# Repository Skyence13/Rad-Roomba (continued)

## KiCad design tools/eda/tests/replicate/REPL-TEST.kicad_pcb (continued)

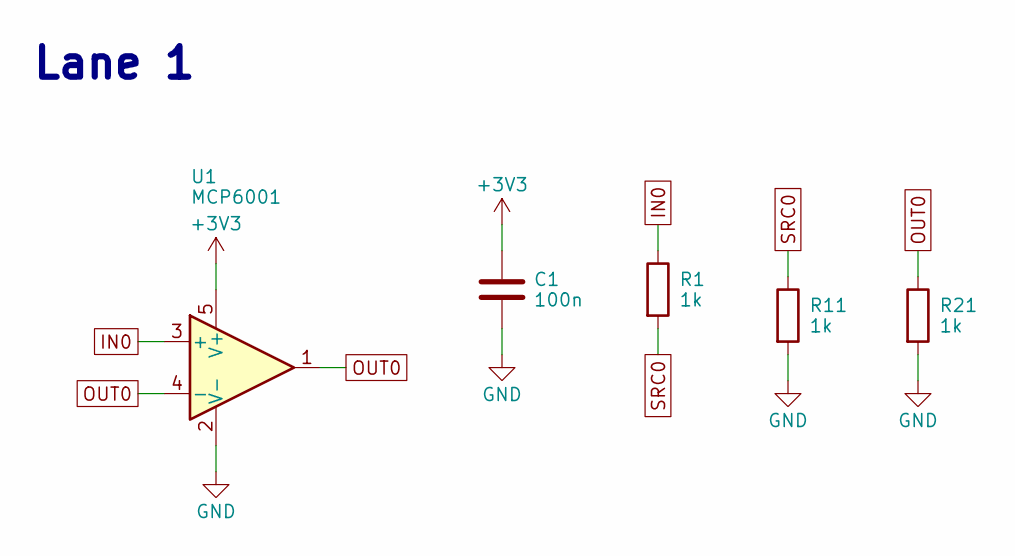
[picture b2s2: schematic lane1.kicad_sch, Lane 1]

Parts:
C1: 100n; C_0402_1005Metric; MPN GRM155R71C104KA88D
R1, R11, R21: 1k; R_0402_1005Metric; MPN RC0402FR-071KL
U1: MCP6001; SOT-23-5; MPN MCP6001T-I/OT

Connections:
+3V3: C1.1, U1.5 (V+); also elsewhere on the board
GND: C1.2, R11.2, R21.2, U1.2 (V-); also elsewhere on the board
IN0: R1.1, U1.3 (+)
OUT0: R21.1, U1.1, U1.4 (-)
SRC0: R1.2, R11.1

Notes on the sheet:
Lane 1

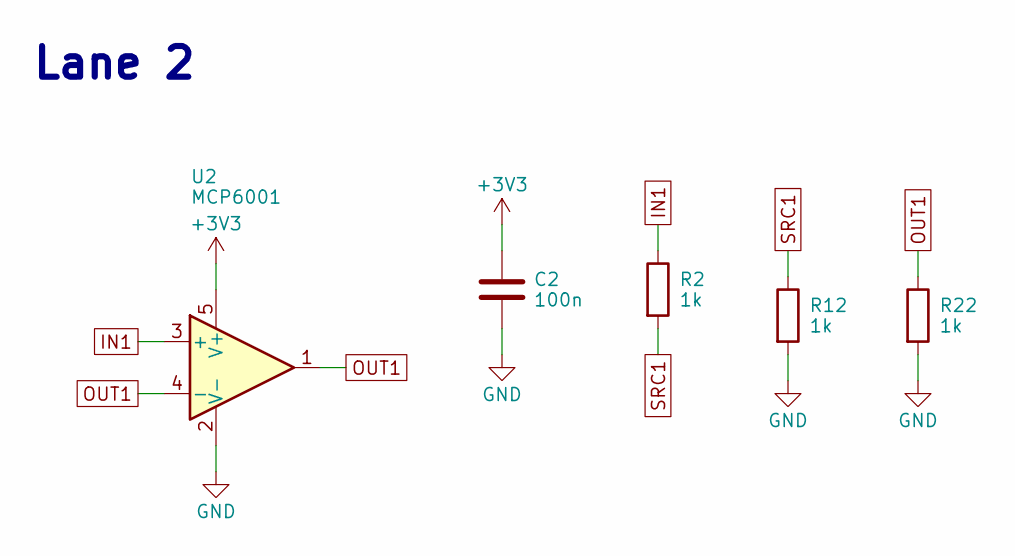
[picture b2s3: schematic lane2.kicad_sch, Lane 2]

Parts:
C2: 100n; C_0402_1005Metric; MPN GRM155R71C104KA88D
R2, R12, R22: 1k; R_0402_1005Metric; MPN RC0402FR-071KL
U2: MCP6001; SOT-23-5; MPN MCP6001T-I/OT

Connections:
+3V3: C2.1, U2.5 (V+); also elsewhere on the board
GND: C2.2, R12.2, R22.2, U2.2 (V-); also elsewhere on the board
IN1: R2.1, U2.3 (+)
OUT1: R22.1, U2.1, U2.4 (-)
SRC1: R2.2, R12.1

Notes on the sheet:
Lane 2

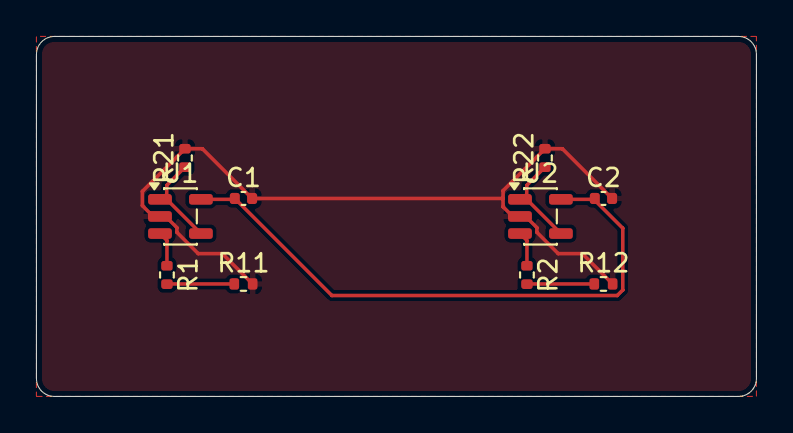
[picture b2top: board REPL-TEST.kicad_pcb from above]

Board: 2 copper layers, 40.0 x 20.0 mm, 10 parts (0 on the bottom side), 8 nets.

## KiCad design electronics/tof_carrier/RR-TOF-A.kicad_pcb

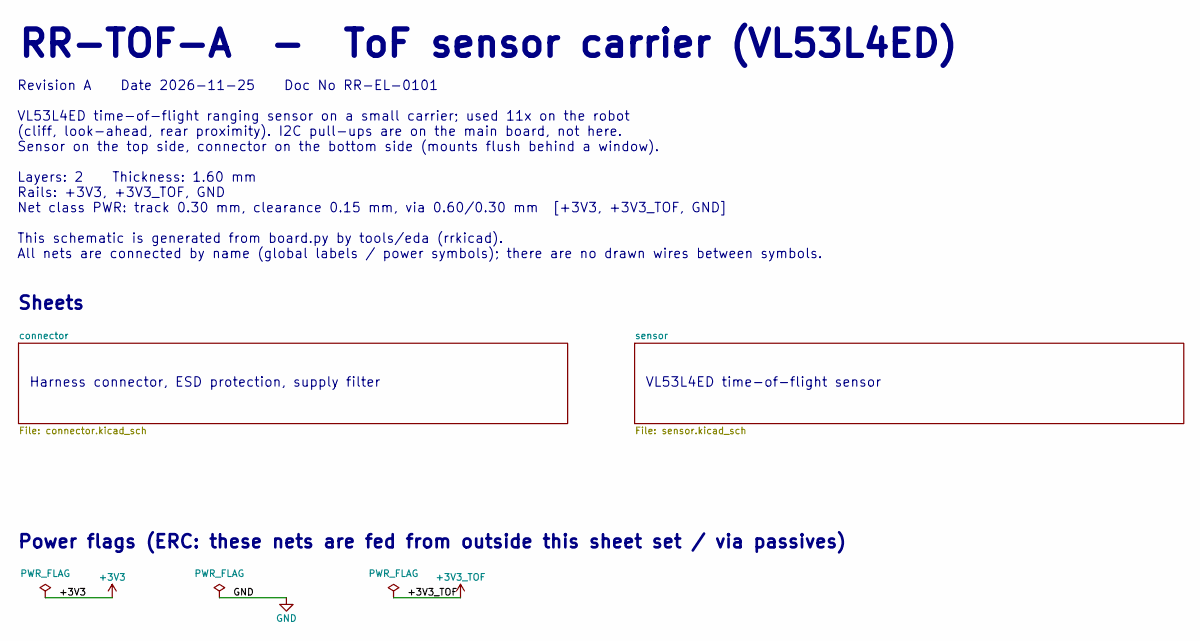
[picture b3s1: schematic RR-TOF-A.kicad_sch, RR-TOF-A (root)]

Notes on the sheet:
RR-TOF-A - ToF sensor carrier (VL53L4ED)
Revision A Date 2026-11-25 Doc No RR-EL-0101 VL53L4ED time-of-flight ranging sensor on a small carrier; used 11x on the robot (cliff, look-ahead, rear proximity). I2C pull-ups are on the main board, not here. Sensor on the top side, connector on the bottom side (mounts flush behind a window). Layer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
Sheets
Harness connector, ESD protection, supply filter
VL53L4ED time-of-flight sensor
Power flags (ERC: these nets are fed from outside this sheet set / via passives)

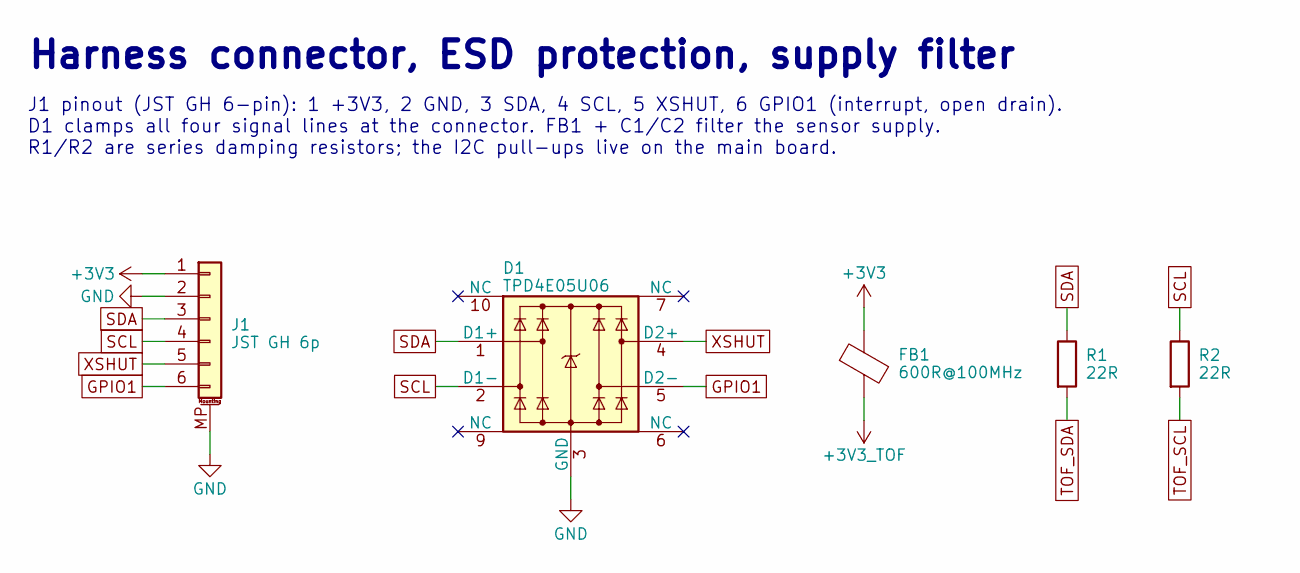
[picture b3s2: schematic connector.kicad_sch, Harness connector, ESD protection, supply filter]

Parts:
D1: TPD4E05U06; USON-10_2.5x1.0mm_P0.5mm; MPN TPD4E05U06DQAR
FB1: 600R@100MHz; L_0603_1608Metric; MPN BLM18AG601SN1D
J1: JST GH 6p; JST_GH_SM06B-GHS-TB_1x06-1MP_P1.25mm_Horizontal; MPN SM06B-GHS-TB(LF)(SN)
R1, R2: 22R; R_0402_1005Metric; MPN RC0402FR-0722RL

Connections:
+3V3: FB1.1, J1.1
+3V3_TOF: FB1.2; also elsewhere on the board
GND: D1.3 (GND), D1.8 (GND), J1.2, J1.MP (MountPin); also elsewhere on the board
GPIO1: D1.5 (D2-), J1.6; also elsewhere on the board
SCL: D1.2 (D1-), J1.4, R2.1
SDA: D1.1 (D1+), J1.3, R1.1
TOF_SCL: R2.2; also elsewhere on the board
TOF_SDA: R1.2; also elsewhere on the board
XSHUT: D1.4 (D2+), J1.5; also elsewhere on the board

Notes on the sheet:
Harness connector, ESD protection, supply filter
J1 pinout (JST GH 6-pin): 1 +3V3, 2 GND, 3 SDA, 4 SCL, 5 XSHUT, 6 GPIO1 (interrupt, open drain). D1 clamps all four signal lines at the connector. FB1 + C1/C2 filter the sensor supply. R1/R2 are series damping resistors; the I2C pull-ups live on the main board.

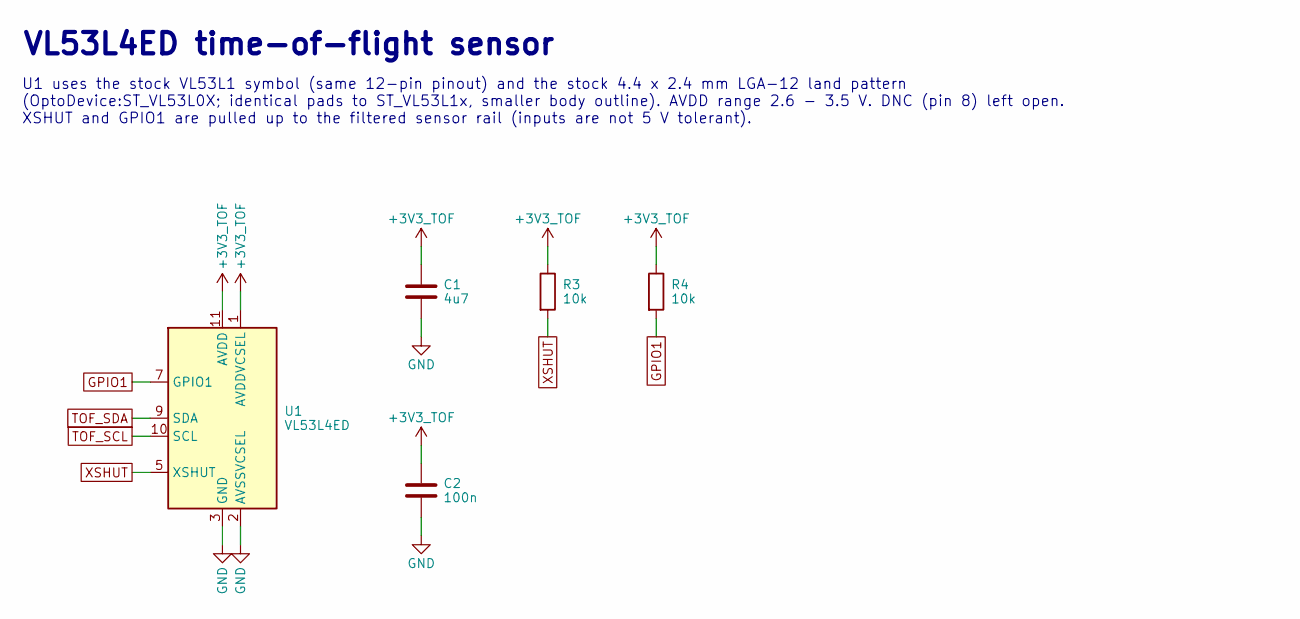
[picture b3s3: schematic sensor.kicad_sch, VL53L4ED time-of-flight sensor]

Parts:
C1: 4u7; C_0603_1608Metric; MPN GRM188R61A475KE15D
C2: 100n; C_0402_1005Metric; MPN GRM155R71C104KA88D
R3, R4: 10k; R_0402_1005Metric; MPN RC0402FR-0710KL
U1: VL53L4ED; ST_VL53L0X; MPN VL53L4EDV0DH/1

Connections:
+3V3_TOF: C1.1, C2.1, R3.1, R4.1, U1.1 (AVDDVCSEL), U1.11 (AVDD); also elsewhere on the board
GND: C1.2, C2.2, U1.2 (AVSSVCSEL), U1.3 (GND), U1.4 (GND), U1.6 (GND), U1.12 (GND); also elsewhere on the board
GPIO1: R4.2, U1.7 (GPIO1); also elsewhere on the board
TOF_SCL: U1.10 (SCL); also elsewhere on the board
TOF_SDA: U1.9 (SDA); also elsewhere on the board
XSHUT: R3.2, U1.5 (XSHUT); also elsewhere on the board

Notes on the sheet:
VL53L4ED time-of-flight sensor
U1 uses the stock VL53L1 symbol (same 12-pin pinout) and the stock 4.4 x 2.4 mm LGA-12 land pattern (OptoDevice:ST_VL53L0X; identical pads to ST_VL53L1x, smaller body outline). AVDD range 2.6 - 3.5 V. DNC (pin 8) left open. XSHUT and GPIO1 are pulled up to the filtered sensor rail (inputs are not 5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

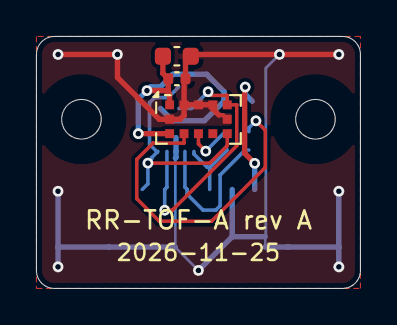
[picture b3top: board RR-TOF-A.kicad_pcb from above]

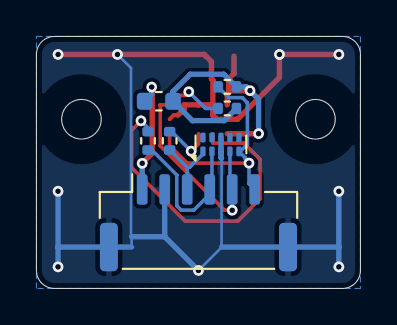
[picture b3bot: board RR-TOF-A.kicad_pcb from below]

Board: 2 copper layers, 18.0 x 14.0 mm, 12 parts (7 on the bottom side), 9 nets.

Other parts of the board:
H1, H2: M-hole 2.2mm; MountingHole_2.2mm_NPTH

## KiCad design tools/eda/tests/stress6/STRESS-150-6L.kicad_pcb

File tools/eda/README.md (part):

# rrkicad — scripted, headless KiCad 9 flow

One Python **board definition** (`electronics/<board>/board.py`) is the single source of
truth. From it the tool generates a native KiCad 9 project (schematic, PCB, project
file), autoroutes it, runs ERC/DRC and writes all fabrication / documentation outputs.
Nothing needs a GUI or network access; KiCad and Freerouting run in Docker.

```
python3 tools/eda/rrkicad.py build electronics/<board>/board.py   # everything
python3 tools/eda/rrkicad.py build .../board.py --no-route        # generate + check, no autorouter
python3 tools/eda/rrkicad.py build .../board.py --reroute         # ignore the cached route
python3 tools/eda/rrkicad.py sch   .../board.py                   # schematic + ERC + PDF only (fast)
python3 tools/eda/rrkicad.py check .../board.py                   # re-run ERC/DRC on the existing files
```
Options for `build`: `--passes N --threads N --timeout SEC` (override the definition's
autorouter settings), `--budget SEC` (wall-clock budget for all autorouter runs, see
"Long routing jobs"). Exit code 0 = pass, 1 = checks failed, 2 = definition error.

Requirements on the host: `python3`, `docker`, images `kicad/kicad:9.0` and
`ghcr.io/freerouting/freerouting:latest` (tested: KiCad 9.0.9, Freerouting 2.6.0).
Wrappers (use them for anything ad hoc, they handle mounts, uid and HOME):
`tools/docker/kicad.sh <cmd...>` and `tools/docker/freerouting.sh in.dsn out.ses [passes] [threads]`.
Both mount the repository at the same absolute path, run as the calling uid with
`--network none`, and work only on files inside the repository.

## What happens in a build

| step | where | what |
|---|---|---|
| 1 `_gen` | KiCad container | evaluate `board.py`; resolve symbols; write `.kicad_pro`, `sym-lib-table`, `fp-lib-table`, `rr_local.kicad_sym`, `rr_local.pretty/`, root + one `.kicad_sch` per group; export the KiCad netlist from the generated schematic and **cross-check it pin-by-pin against the definition**; build the unrouted `.kicad_pcb` with pcbnew (pad nets come from that netlist); auto-arrange unplaced parts; copy replicated blocks; plane fan-out vias; export `route/<name>.dsn` (with 25 um extra clearance and edge keep-outs for the autorouter) |
| 2 route | Freerouting container | `route/<name>.dsn` → `route/<name>.ses` (+ `freerouting.log`, `route_meta.json`). Skipped when the DSN hash is unchanged and a SES exists (so reruns are deterministic); `--reroute` forces it |
| 3 `_post` | KiCad container | import SES into the pristine generated board (separate process), verify pre-routes are untouched, replay `route/finish.json`, widen tracks the router necked below the fab minimum, remove dangling stubs (and unused escape vias on a fully connected board), fill zones, add fab notes/dimensions, save; ERC; DRC with schematic parity; outputs; `reports/summary.json`, `reports/open_connections.txt` |
| 4 continue / restart | both | only while connections are open: continue runs from the routed board, fresh restarts with other seeds, optionally within `--budget` (quick imports in between, best SES kept; see "Completion strategy" and "Long routing jobs") |
| 5 finisher | KiCad container | only while connections are still open: maze router with rip-up, then step 3 again |

Files per board directory:
```
board.py                       the definition (edit this, nothing else)
<name>.kicad_pro/.kicad_sch/.kicad_pcb, <group>.kicad_sch, rr_local.*, *-lib-table, 3d/   generated KiCad project
route/      <name>.dsn, <name>.ses (routing result = cache key + source of the tracks), freerouting.log,
            route_meta.json, progress.log (one JSON line per autorouter run), finish.json (finisher
            result), blocks.json (replicate), escape_vias.json (intermediate)
reports/    erc.json/.rpt, drc.json/.rpt, summary.json, placement.txt, build_state.json
out/        <name>-schematic.pdf, gerber/ (Gerbers, Excellon PTH/NPTH, drill maps, .gbrjob),
            <name>-pos.csv, <name>-bom.csv, <name>-fab.pdf, <name>-assembly-top/bottom.pdf,
            <name>-copper.pdf, <name>.step, <name>-render-top/bottom.png, pinmap.json, <name>.net
```
`reports/summary.json`: `status` (`pass`/`fail`), `fail_reasons`, ERC/DRC error/warning
counts by type, `unconnected`, `parity`, `unrouted_nets`, every waiver with its
justification and match count, auto-added `pwr_flags`, `single_pin_nets`, BOM lines
missing an MPN or flagged `verify`, routing statistics, and the output list.
**Fail** = any ERC error, DRC error, unconnected item or schematic-parity item that is
not waived. Warnings never fail the build but are counted.

`out/pinmap.json`: for every part pin: `pin`, `name`, `net` (null = no-connect), `type`,
`pad_xy_mm` (board frame) and `side`; plus a `nets` → `["REF.pin"]` index.

## Conventions

* Units: mm. **Board frame: X right, Y up**, origin = the point you define the outline
  against; it becomes the KiCad drill/place (aux) origin and grid origin, so
  `board.py`, the pick-and-place file, the STEP model and `pinmap.json` share coordinates.
* `at=(x, y, rot, side)`: `rot` is the KiCad footprint orientation in degrees (CCW
  positive), `side` `"F"` or `"B"`. For bottom parts it is the value KiCad shows for the
  flipped footprint — check the result in `pinmap.json` (`pad_xy_mm`) rather than guessing
  (e.g. the JST GH on RR-TOF-A needed `rot=180` on the bottom to face the edge).
* Net names are global: the same string anywhere is the same net. PCB net names equal
  the names in `board.py`.
* Schematic style: one A3 sheet per group (extra sheets are added automatically when a
  group overflows). Every used pin has a short stub ending in a global label, or a power
  symbol for nets declared with `board.rail()`. Unused pins get no-connect flags. Nets
  that have power-input pins but no power-output pin get a `PWR_FLAG` on the root sheet
  (listed in the summary as `pwr_flags`).
* Reference designators are yours to assign; they must be unique.
* Every symbol pin must be either in `pins`, in `nc`, of type no_connect, or the part
  must say `unused="nc"`; otherwise the build stops and lists the pins.

## Board definition by example

```python
from rrkicad import Board, Pad, SymPin, Rules

board = Board("RR-XYZ-A", title="Example board", rev="A", date="2026-11-25", docnum="RR-EL-0123",
              company="Rad Roomba", layers=4,          # 2, 4 or 6:
                                                        #   4 = F.Cu sig / In1 plane / In2 plane / B.Cu sig
                                                        #   6 = F.Cu sig / In1 GND / In2 sig / In3 sig / In4 PWR / B.Cu sig
              thickness=1.6, silk_refs=True,            # False hides all reference designators on silk
              rules=Rules(),                            # fab rules, see "Rules" below
              paper="A3", description="free text shown on the root sheet")

# --- nets ----------------------------------------------------------------------
board.rail("+5V", "+3V3", "GND")                      # drawn with power symbols (stock power:<name> or generated)
board.netclass("PWR", ["+5V", "+3V3", "GND", "VBAT*"],  # exact names or KiCad wildcards
               track=0.4, clearance=0.2, via_dia=0.8, via_drill=0.4)

# --- parts: one group = one schematic sheet --------------------------------------
g = board.group("mcu", "Microcontroller", notes="Text block printed at the top of the sheet.")
g.part("U1", "MCU_ST_STM32G4:STM32G474RETx", "STM32G474RET6",        # ref, symbol, value
       footprint=None,                      # default: the symbol's Footprint property
       mfr="STMicroelectronics", mpn="STM32G474RET6",
       pins={"VDD": "+3V3", "VSS": "GND",   # key = pin NAME (all pins with that name) ...
             "7": "NRST", "PA0": "ADC0"},   # ... or pin NUMBER (numbers win)
       nc=["PC13"], unused="nc",            # explicit NC pins; unused="nc" marks all remaining pins NC
       at=(50, 40, 0, "F"),                 # omit -> auto-arranged
       notes="BOM note", verify=True,       # verify=True -> "verify: true" in the BOM notes
       dnp=False, bom=True, datasheet="https://...", description="...",
       fields={"Tolerance": "1%"},          # extra symbol/footprint fields
       sch_rot=0,                           # symbol rotation on the sheet (0/90/180/270)
       silk_ref=False,                      # per part: False | True | (x, y[, rot[, size]])
       zone_connect="solid",                # pads of this part: "solid" | "thermal" | "none"
       height=1.6,                          # body height (mm) for the generated 3D envelope, see "3D"
       model=None)                          # or a real model: "${KIPRJMOD}/3d/part.step"
g.C("C1", "100n", "+3V3", "GND", pkg="0402", mfr="Murata", mpn="GRM155R71C104KA88D", near="U1.16")
g.R("R1", "10k", "+3V3", "NRST", mfr="Yageo", mpn="RC0402FR-0710KL")           # pkg default 0402
g.FB("FB1", "600R@100MHz", "+3V3", "VDDA", pkg="0603", mfr="Murata", mpn="BLM18AG601SN1D")
g.L("L1", "10u", "SW", "VOUT", pkg="0805", mfr="...", mpn="...")
g.LED("D1", "green", "LED_A", "GND", pkg="0603", mfr="...", mpn="...")       # anode, cathode
# R/C/L/FB/LED accept every part() keyword (at=, near=, dnp=, ...).  pkg: 0201 0402 0603 0805 1206 1210 2010 2512

# identical blocks: place (or auto-arrange) one block, copy its placement AND routing at an offset
# (see "Replicating blocks" below)
# board.replicate((lane1_group, lane2_group), dx=80.0, dy=0.0)     # groups with the same parts in the same order
# board.replicate({"U1": "U101", "C1": "C101"}, dx=80.0)          # or an explicit {source_ref: destination_ref} map

# auto-arrange hints for parts without at=:
#   near="U1" | near="U1.16" (pad 16 of U1)   edge="left|right|top|bottom"   side="B"   rot=90 (fixed rotation)
# rail-to-rail capacitors without near= are spread over the supply pins of the ICs in their group.

# --- outline, holes, copper ------------------------------------------------------
board.outline_rect(100, 80, radius=2.0, origin="corner")   # origin "corner" (lower-left) or "center"
# board.outline_poly([(x, y), ...], radius=1.0)            # any closed polygon, every corner rounded
board.cutout_rect(50, 76, 12, 3, radius=1.0)               # centre x, y, w, h   (also cutout_circle, cutout_poly)
board.hole("H1", 4, 4, drill=3.2, keepout=7.0)             # NPTH + circular keep-out (tracks/vias/pour/parts)
board.hole("H2", 96, 4, drill=3.2, plated=True, pad=6.0, net="GND")
board.zone("GND", ["In1.Cu"], connect="solid")             # polygon=None -> whole board
board.zone("+3V3", ["In2.Cu"], connect="solid")
board.zone("+5V", ["In2.Cu"], polygon=[(0, 0), (30, 0), (30, 30), (0, 30)], priority=1)  # plane split
board.zone("GND", ["F.Cu", "B.Cu"])                        # pours; options: clearance, min_width,
                                                           # connect thermal|solid|none, thermal_gap/width, islands
board.keepout("KO_ANT", polygon=[(80, 60), (92, 60), (92, 72), (80, 72)],   # or circle=(x, y, dia)
              layers=("*.Cu",), tracks=True, vias=True, copper=True, pads=False, footprints=True)
board.track("XTAL_IN", [(10, 10), (12, 10), (13, 11)], layer="F.Cu", width=0.2)  # pre-route: locked, kept by the router
board.via("GND", 20, 20)                                   # pre-route via (net-class size unless dia=/drill=)
board.text("{name} rev {rev} {date}", 50, 2, layer="F.SilkS", size=1.0)   # also {title} {docnum}; B.* is mirrored
board.fab_note("Controlled impedance not required.")       # extra line on the fabrication drawing

# --- project-local library (parts missing from the stock libraries) -----------------
sym = board.symbol("MYSENSOR", [SymPin(1, "VDD", "power_in", "T"), SymPin(2, "OUT", "output", "R"),
                                SymPin(3, "GND", "power_in", "B"), SymPin(4, "EN", "input", "L")],
                   ref_prefix="U", datasheet="https://...")                  # -> "rr_local:MYSENSOR"
fp = board.footprint("MYSENSOR_LGA4", [Pad(1, -1.0, -0.8, 0.6, 0.9), Pad(2, 1.0, -0.8, 0.6, 0.9),
                                       Pad(3, 1.0, 0.8, 0.6, 0.9), Pad(4, -1.0, 0.8, 0.6, 0.9)],
                     body=(2.0, 1.2))                                        # -> "rr_local:MYSENSOR_LGA4"
g.part("U9", sym, "MYSENSOR", fp, mfr="...", mpn="...", pins={"VDD": "+3V3", "OUT": "S1", "GND": "GND", "EN": "+3V3"})

# --- autorouter / auto-arrange / waivers ---------------------------------------------
board.route(passes=100, threads=None, timeout=None, optimizer=True, enabled=True, extra_args=[],
            plane_fanout=True,     # rrkicad's own track+via beside every SMD pad of plane nets (see Routing notes)
            retries=2,             # extra "continue" autorouter runs while connections are open
            restarts=1,            # then fresh autorouter runs with another item-order seed (best result kept)
            fanout=False,          # Freerouting's own fan-out stage (escape via on every SMD pin; rarely useful)
            escape="auto",         # fine-pitch escape (see Routing notes): "auto" = on for 4/6 layers, True, False
            escape_pitch=0.65,     #   ICs whose pad pitch is below this get escaped ...
            escape_min_pads=16,    #   ... and that have at least this many perimeter pads
            escape_via=None,       #   (dia, drill) of escape vias; default = the fab minimum via of Rules
            escape_track=None,     #   stub width; default Rules.min_track
            escape_layers=None,    #   informational: target layer recorded per via (through vias reach all layers)
            escape_direct=True,    #   short direct pre-route to a nearby two-pad passive instead of a via
            finisher=True,         # built-in maze router for the last open connections (see Routing notes)
            finisher_ripup=True,   #   ... allowed to rip up and reroute autorouter copper of other signal nets
            finisher_seconds=900,  #   ... time budget
            budget=None,           # wall-clock budget (s) for all autorouter runs (also: build --budget SEC)
            chunk=900,             #   with a budget: cap per Freerouting run (each run leaves an SES on disk)
            stall=2,               #   with a budget: stop after this many continue runs without improvement
            zone_nets="auto",      # "auto" = "exclude" on 4/6 layers: nets with a copper zone are never autorouted
            fr_fallback="none")    # Freerouting's own fallback strategies after stagnation (see Routing notes)
# per part: g.part(..., escape=None | True | False)   None = decided by pad pitch, True = force, False = never
board.autoplace_options(clearance=0.3, ic_halo=2.0, edge_margin=0.5, grid=0.25, spread=0.35, rotations=(0, 90, 180, 270),
                        escape_keepaway=2.0)   # free band (mm) around the courtyard of escaped ICs (auto-arranged neighbours)
board.waive("drc", "silk_overlap", "Reference text overlaps on the dense RF corner; assembly uses the Fab layer.",
            match=r"R1[0-9]")                             # regex on the violation text; None = all of that type
board.severity("drc", "silk_over_copper", "ignore", "Silk is clipped by the fab's solder-mask subtraction.")
```
The file must leave the `Board` in a module-level variable named `board`. It is plain
Python evaluated **inside the KiCad container** (Python 3.11): loops, helper functions
and `from rrkicad.symlib import SymbolLibs` (to look at stock symbol pins) are fine.

### Stock libraries
Symbols `Library:Name` and footprints `Library:Name` refer to the KiCad 9 stock
libraries in the container (`/usr/share/kicad/symbols`, `/usr/share/kicad/footprints`).
Unknown names stop the build with close-match suggestions. To browse:
`tools/docker/kicad.sh bash -c 'ls /usr/share/kicad/footprints/Package_SO.pretty | head'`,
or print a symbol's pins:
```
tools/docker/kicad.sh python3 -c "from rrkicad.symlib import SymbolLibs
for p in SymbolLibs().get('Device:R').pins: print(p.number, p.name, p.etype, p.unit)"
```
Multi-unit symbols are placed unit by unit automatically (map their pins by number).
Derived symbols (`extends`) are flattened like KiCad does.

### Local symbols / footprints
* `SymPin(number, name, etype="passive", side="L", unit=1)` — `etype` is a KiCad pin
  type (`input output bidirectional tri_state passive power_in power_out open_collector
  open_emitter no_connect unspecified free`); `side` L/R/T/B, pins are stacked in list
  order at 2.54 mm pitch; several `unit` values make a multi-unit symbol.
* `Pad(number, x, y, w, h=None, shape="roundrect", kind="smd", drill=None, rot=0, rratio=0.25, paste=True)`
  — coordinates in the **footprint editor frame (x right, y DOWN, top view)**; `shape`
  rect/roundrect/circle/oval; `kind` smd/thru/npth. `board.footprint(..., body=(w, h),
  courtyard=(w, h), pin1=True, model="${KIPRJMOD}/3d/x.step")`. Fab outline, courtyard,
  silk lines clear of pads and a pin-1 dot are generated. A footprint without pads (e.g. a
  shield-can outline) is allowed when it has `body=` or `courtyard=`.
* Mounting holes from `board.hole()` are generated footprints in `rr_local.pretty`
  (board-only, no courtyard; the keep-out rule area protects them).
* Generated rail symbols (rails with no stock `power:` symbol) also live in `rr_local.kicad_sym`.

### Rules
`Rules(min_track=0.15, min_clearance=0.15, min_via_dia=0.6, min_via_drill=0.3, min_annular=0.13,
edge_clearance=0.3, min_hole=0.3, min_hole_clearance=0.25, min_hole_to_hole=0.25, track=0.2,
clearance=0.15, via_dia=0.6, via_drill=0.3, min_silk_text=0.8, min_silk_thickness=0.1)` —
written to the project's board setup and the `Default` net class; `netclass()` adds
classes on top (first matching pattern wins).

## Routing notes
* **Plane fan-out (4/6 layers).** For every net that has a zone on a plane layer
  (`In1/In2` on 4 layers, `In1/In4` on 6) the PCB step itself adds a short locked track
  and a via beside each SMD pad of that net (through-hole pads connect to the plane
  directly). The via respects copper clearance, hole-to-hole, edge clearance, cut-outs,
  via keep-outs and other parts' courtyards where possible, and must land inside its
  own net's plane polygon (split planes). Clearances are pairwise (the larger of both net
  classes, like KiCad's DRC); footprint-internal rule areas and copper drawn inside
  footprints (net ties) are obstacles. Exposed/thermal pads get their via in the pad centre.
  **Long fan-out:** a pad with no legal via position beside it is connected by the maze
  router (see Finisher) to the nearest legal via position inside its own plane polygon
  (windows 5 / 12 / 30 mm), as locked pre-route; `summary.json` → `routing.plane_fanout`
  lists them (`long_fanout`) and the pads still without a connection (`failed`, with the
  reason). After zone fill, KiCad's DRC connectivity check is what confirms every plane
  connection (`unconnected` must be 0).
* **Zone nets are not autorouted (4/6 layers, `zone_nets="auto"`).** Every net that has a
  copper zone is moved into a DSN net class `RR_ZONE_<class>` that Freerouting is told to
  ignore (`--router.autorouter.ignore_net_classes`); its pads connect through the plane
  fan-out / long fan-out and the zone fill only. Whatever stays open is left to the finisher
  and reported. On 2-layer boards (`"auto"` = `"route"`) zone nets are routed as tracks and
  the pour is added afterwards (RR-TOF-A, RR-PANEL).
  Split planes must be **non-overlapping polygons** (Freerouting rejects overlapping
  plane areas; do not rely on zone priority for splits).
  If you also pour a plane net on the outer layers, use `connect="solid"` for that pour
  (or leave the outer layers unpoured): thermal spokes next to fan-out tracks get starved.
* **Fine-pitch escape (4/6 layers by default).** Before routing, every IC whose pad pitch is
  below `escape_pitch` (0.65 mm; QFP, QFN, TSSOP-0.5, ...) and has at least
  `escape_min_pads` (16) perimeter pads, or that has `escape=True`, gets
  its pin escapes as locked pre-routes (`rrkicad/escape.py`):
  - signal pads: a short stub (`escape_track`, default `min_track`) out of the pad tip and a
    via on a ring outside the package, alternating between two staggered radii. The ring is
    *fanned*: neighbouring vias are spaced by via radius + half stub + clearance of the two
    nets, so the stub of an outer-row via passes between two inner-row vias with full
    clearance even with 0.6 mm vias at 0.5 mm pitch (the inner radius grows until every
    outer stub clears its neighbours' vias). Pads whose planned spot is blocked get a local
    search over further radii / lateral offsets, then (packages without exposed pad) a
    position under the package;
  - plane-net pads: via *under* the package for QFP-like parts (keeps the ring free),
    otherwise a ring position whose via lies inside the net's own plane polygon;
  - pads whose net reaches a two-pad passive (pull-up, series R placed `near=` the pin)
    within 4 mm: a direct pre-route to that pad instead of a via, when one or two straight
    segments do it with clearance (`escape_direct`);
  - skipped (listed with the reason in `summary.json` → `routing.escape.skipped`):
    no-connect pins, pins tied only to an adjacent pin, square/round pads (BGA), and pads
    with no legal position (left to the autorouter, also listed as a build note; for zone nets on
    4/6 layers: left to the finisher).
  All checks are exact geometry (`rrkicad/geom.py`): copper clearance of both net classes
  + the 25 um DSN margin, hole-to-hole, hole clearance, board edge, cut-outs, via
  keep-outs, other parts' courtyards (vias stay outside them), existing fan-out vias. The
  items are exported to the DSN as fixed wiring *of their net*, so Freerouting starts from
  the escape vias. `summary.json` → `routing.escape`: per part pitch / ring / inward / direct
  / skipped counts, totals, via and stub size. Escape vias the router did not use (it
  connected at the pad instead) are removed with their stub after the SES import (only
  escape vias, only if connectivity does not get worse). The escape runs before the plane
  fan-out; the plane fan-out puts a via in the centre of exposed/thermal pads.
  Small fine-pitch parts (< 16 pads: USON-10 ESD arrays, SOT-563, ...) are left to the
  autorouter by default: it escapes them reliably, and a via ring around a flow-through
  ESD array works against its layout; force one with `escape=True`.
  The auto-arranger keeps `escape_keepaway` (2 mm) free around
  escaped ICs; explicitly placed neighbours are the author's responsibility (a pad whose
  via would land in a neighbour's courtyard is skipped and reported).
* **Finisher.** If connections are still open after the autorouter (and its continue runs),
  `finisher=True` runs a plain grid maze router (A*, 0.05 mm grid, 8 directions, through
  vias between signal layers, never on plane layers) for each open connection KiCad's DRC
  reports, on a clearance-inflated occupancy grid (both net classes' clearance + half the
  track width; vias against copper on every layer, drills, same-net SMD pads; edge,
  cut-outs, keep-outs), in a window that grows 6 mm -> 15 mm -> whole board. Every path is
  re-checked with exact geometry before it is added. If there is no free path and
  `finisher_ripup=True` (default), it searches again allowing to cross *unlocked autorouter
  copper of other signal nets* at a cost, rips up what the new path violates, and
  reconnects every ripped net (which may in turn rip up further autorouter copper, never
  pre-routes, escape/fan-out copper, nets with zones or the finisher's own new copper);
  at most 40 steps per open connection (`finisher_seconds` caps the whole finisher), and the whole transaction is undone if any ripped
  net cannot be reconnected. Results go to `route/finish.json`
  (added items and ripped-up items, keyed to the SES hash, re-applied on cached builds; keep
  it under version control with the SES); `summary.json` → `routing.finisher` lists what it routed and what not and why.
  DRC checks the result like everything else; nothing is ever marked connected by the
  finisher itself. Slow in Python on large windows (minutes per hopeless connection).
* Freerouting reports "N pin-to-pin clearance violations" in `route/freerouting.log` for
  QFN exposed pads vs. their perimeter pads: that is the footprint's own pad spacing under
  the 25 um DSN margin, fixed items it cannot change; KiCad DRC is the reference.
* Freerouting's fallback strategies after stagnation (default chain ending in
  `continue-auto-neck`; even `continue` re-routes from the initial board) can eat the whole
  timeout: rrkicad passes `--router.autorouter.fallback_strategies=none` unless
  `route(fr_fallback=...)` or `extra_args` say otherwise - its own continue runs and restarts
  do that job and keep the best result.
* The autorouter gets keep-out bands along the outline and around cut-outs so routed
  copper keeps the board-edge clearance, and via keep-outs (plus track keep-outs on their
  layer, minus the tie's pads) over copper drawn inside footprints (net ties) - Freerouting
  does not see that copper. Rule areas that ban neither tracks nor vias (e.g. a "no
  footprints" area) are not exported to the router (KiCad would export them as full
  routing keep-outs).
* Pre-routes (`board.track`, `board.via`) and the plane fan-out are locked, exported as
  fixed, and verified after the SES import; the build fails if the router changed them.
* **Completion strategy.** If connections are still open after the first run, the build
  automatically lets Freerouting *continue from the routed result* (new DSN from the
  routed board; fresh rip-up budget concentrated on the failed nets), up to
  `retries` times, keeping a run only if it reduces the open count. Each continue run uses
  a different Freerouting item-order seed (`--router.autorouter.item_order_seed`); a run
  that does not improve is discarded and the next seed is tried. If connections are still
  open after that, Freerouting starts once more from scratch with another item-order seed
  (`restarts`, default 1; a fresh run is deterministic for a given DSN and seed, so repeating
  it unchanged is pointless) followed by its own continue runs; the result with fewer open
  connections is kept. Then the finisher (below) takes what is left. Freerouting itself
  also switches strategy when it stagnates (visible in `route/freerouting.log`).
  What is still open afterwards is reported, never hidden: `summary.json` →
  `drc.unrouted` lists every open connection with net, both end items and their board
  coordinates (also printed as `OPEN ...` lines), `routing.autorouter.attempts` lists
  the runs. A board with open connections is always FAIL.
* Giving Freerouting a `timeout` is safe: it is passed as Freerouting's own job timeout
  (verified: it stops and still writes the result); a hard kill follows 3 min later.
* The routing result lives in `route/<name>.ses` (+ `route_meta.json` with the DSN
  hash). Keep both under version control: with an unchanged definition the build
  re-uses them and reproduces the same PCB. `route/<name>.unrouted.kicad_pcb` is an
  intermediate file and need not be kept.

## Long routing jobs (large boards)
`python3 tools/eda/rrkicad.py build board.py --budget 2400` (or `route(budget=2400)`):
* every Freerouting run is capped at `chunk` seconds (default 900) and writes a scratch SES;
  it is imported with a quick import (connectivity count only, no ERC/DRC/outputs) and
  replaces `route/<name>.ses` only if it leaves fewer connections open. So
  `route/<name>.ses` always holds the best state so far - an interrupted job loses at most
  the run in progress; a later plain `build` re-uses it (DSN unchanged);
* after the first run, continue runs resume from the best routed board (new DSN exported
  from it), each with another item-order seed, until the budget is used up (less than
  3 min left) or `stall` runs in a row did not improve; then `restarts` fresh runs if time
  is left; then the finisher (its own `finisher_seconds`); then one full check;
* `route/progress.log`: one JSON line per run (kind, seed, seconds, open count, kept, best,
  elapsed) - `tail -f` it to watch an unattended job;
* the count used everywhere is KiCad's connectivity count after zone fill (`summary.json` →
  `drc.unconnected`; `drc.unconnected_listed` is how many KiCad's DRC report lists, it stops
  at 499).

### Recommended recipe for the final runs on the large boards
1. Placement first: every plane pad needs a via spot within ~4 mm (check `summary.json` →
   `routing.plane_fanout.failed` after `build --no-route`; aim for 0), 2+ mm free around
   fine-pitch ICs if escape is used, no DRC errors before routing.
2. Hand pre-routes (`board.track` / `board.via`) for power trunks, HV, analogue, safety chain.
3. Route lane 0 / the source block, then freeze it with `replicate()` (second build).
4. Unless step 1 reached 0, keep zone nets routable: `route(zone_nets="route")`.
   Escape: `escape="auto"` helps where the fine-pitch ICs have room (stress boards);
   if `routing.escape.skipped` lists many "no legal escape position", use `escape=False`.
5. One long run per DSN: `route(timeout=7200, passes=500, retries=2, restarts=0,
   optimizer=False)` and `build board.py` (no `--budget`): one uninterrupted Freerouting job,
   then continue runs from its result. Use `--budget SEC` (chunks of `chunk` s) only when
   the job must survive interruptions - the best SES is then on disk after every chunk.
6. Watch `route/progress.log`; results: `reports/summary.json` (`drc.unconnected`, `drc.errors`,
   `drc.by_type`), `reports/open_connections.txt` (KiCad's list, max 499), `route/<name>.ses`.
   A later `build` with an unchanged DSN re-uses the SES (and `route/finish.json`) without
   routing; `build --reroute` starts again.
7. Finish the remaining tens of connections in KiCad.

## Replicating blocks (identical lanes/channels)
`board.replicate(pairs, dx, dy, routes=True)` — `pairs` is `{source_ref: destination_ref}`
or a `(source_group, destination_group)` tuple (same parts in the same order).
* Placement: every destination part takes its source's position + (dx, dy), same rotation
  and side. The source block may be placed explicitly or auto-arranged; destinations
  are excluded from auto-arrange. Call it once per copy (lane 0 → 1, 0 → 2, 0 → 3).
* Routing (`routes=True`, default): after each routed build the tracks/vias of the
  **block-internal nets** (nets whose pins all belong to the source parts; rails and
  inter-block nets are excluded) are stored in `route/blocks.json`. The *next* build adds
  them as fixed pre-routes for the source block and, shifted and renamed, for each copy.
  So: build once (autorouter routes everything), build again (blocks frozen and
  identical; the autorouter only has plane leftovers and inter-block nets). If the
  source placement changes, the stored routes are ignored with a note and refreshed by
  the next build. Keep `route/blocks.json` under version control.
* Plane fan-out / escape are generated per pad for the copies as usual and are *not* stored in
  `blocks.json` (only router copper and the definition's own pre-routes are); a stored item
  identical to copper already on the board (e.g. a pre-route the definition draws for every
  lane itself) is not replayed again. (Before 2026-11-27 both happened and gave co-located
  vias; such an old `blocks.json` heals on the next routed build.) Overlaps of a copy with
  foreign parts, tracks or keep-outs show up in DRC, they are not checked at copy time.
* Auto-arrange: when a source part is auto-arranged, the spots of all its copies must be
  free as well and are reserved, so no other part lands where a copy will go.
Tested on `tools/eda/tests/replicate/` (2 lanes, 2 layers) and on a copy of RR-HEAD-ACQ
(`tools/eda/tests/head_escape/`, 4 lanes).

## Importing a stage-1 circuit definition
`rrkicad.importer.from_circuit(board, "design/circuit.py", ...)` converts a tool-neutral
`PARTS` list (dicts with `ref, value, mpn, manufacturer, description, package,
symbol_hint, footprint_hint, pins={pin_number: (pin_name, net) | None}, block, dnp,
notes`, optional `verify`, `height_mm`) into groups (one per `block`) and parts:
```python
from rrkicad import Board
from rrkicad.importer import from_circuit
board = Board("RR-CHS-MAIN", title="...", layers=6, ...)
report = from_circuit(board, os.path.join(os.path.dirname(__file__), "design/circuit.py"),
                      footprints={"U10": "Package_DFN_QFN:...", "MICROFIT-2x2-RA": "Connector_Molex:..."},  # by ref or package
                      symbols={"U42": "rr_local:MYSYM"},        # override the symbol of single parts
                      place={"J_PWR": (8, 50, 90, "F")},        # at= by ref (everything else is auto-arranged)
                      titles={"mcu": "Microcontroller"},        # sheet titles by block
                      allow_missing=False)                      # True: skip parts that have no footprint yet
board.rail("GND", "+3V3", ...); board.netclass(...); board.outline_rect(...); ...
```
Symbol per part: `symbols[ref]`, else `symbol_hint` if that stock symbol exists, has all
pin numbers used and no conflicting stacked pins (a hint `rr_local:NAME` is accepted when
`board.symbol("NAME", ...)` was defined before the import and has all pin numbers), else a
generated local box symbol (all
pins `passive`, named from the MPN). Pins with `None` become no-connects. `report` lists
`hint_rejected` (with the reason), `local_symbols`, `missing_footprints`. Parts can be
tuned afterwards: `board.part("U1").at = ...` is not supported - pass `place=`; other
attributes (`near`, `side`, `edge`, `zone_connect`, `silk_ref`) may be set on
`board.part(ref)` before the build. Reference designators are taken as they are
(`J_PWR`, `R_SH1` work).

Measured (schematic + ERC only, `python3 tools/eda/rrkicad.py sch tools/eda/tests/import_<x>/board.py`):

| circuit.py | parts imported | stock / generated symbols | hints rejected | no footprint | sheets | ERC | time |
|---|---|---|---|---|---|---|---|
| chassis_main (768) | 753 | 710 parts / 18 symbols | 46 | 15 | 18 | 0 errors, 112 warnings | 14 s |
| panel (24) | 24 | 24 / 0 | 0 | 0 | 6 | 0 errors, 0 warnings | 3 s |
| head_acq (1085) | 1081 | 971 parts / 20 symbols | 114 | 4 | 22 | 0 errors, 57 warnings | 17 s |

`reports/import_report.json` in each test directory lists every rejected hint with the
reason (mostly symbol names that do not exist in the stock library, with the closest
matches) and every part without a footprint - that list is the stage-2 to-do list.
Generated symbols have all-passive pins, so ERC cannot check pin directions on them.
No PCB was built from these imports (no placement, rails or outline decisions yet).

## Reproducibility
UUIDs are derived from hashes (schematic) or a seeded generator (PCB), ordering is
stable, report dates are stripped, Gerber/drill/STEP creation dates are set to the board
date. Re-running an unchanged definition reproduces identical KiCad project files.
Not byte-stable: PDFs and PNGs (embedded timestamps) and a *new* Freerouting run (its
optimiser is multi-threaded) — which is why the SES is cached.

## Known limitations
* No drawn wires in the schematic: connectivity is by label/power symbol only (readable,
  but not a hand-drawn schematic). No buses, no hierarchical pins, no symbol mirroring.
* Net labels are always global; there is no per-sheet local net scope.
* 2, 4 or 6 copper layers; through vias only; no differential-pair or length tuning
  (net-class diff-pair fields are written but the autorouter ignores them).
* Fine-pitch escape handles perimeter packages (QFP/QFN/SO/TSSOP); BGA (round pads) is
  skipped. Escape vias are through vias (no blind/buried/micro vias).
* Auto-arrange is a greedy helper (top/bottom side per part, courtyard rectangles). It
  avoids overlaps and keep-outs but knows nothing about signal integrity; place
  connectors, sensitive analogue parts and anything mechanical explicitly.
* `waive()` is tool-level: the item is listed as waived in `summary.json` but the KiCad
  GUI will still show it. `severity()` changes the project rule severity and is visible
  in the GUI too. Both require a written reason.
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
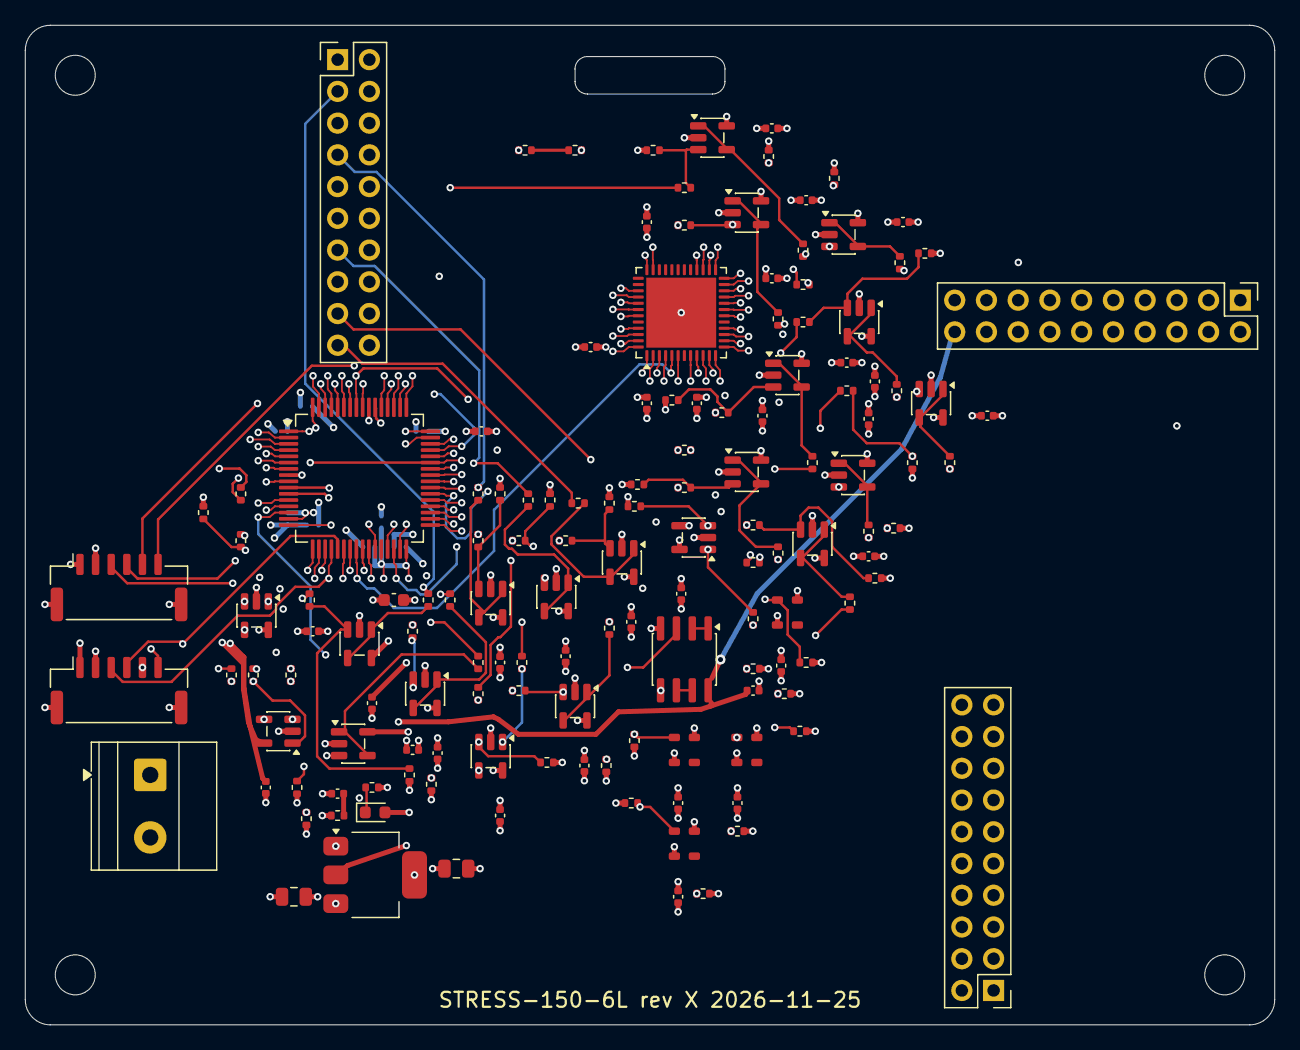
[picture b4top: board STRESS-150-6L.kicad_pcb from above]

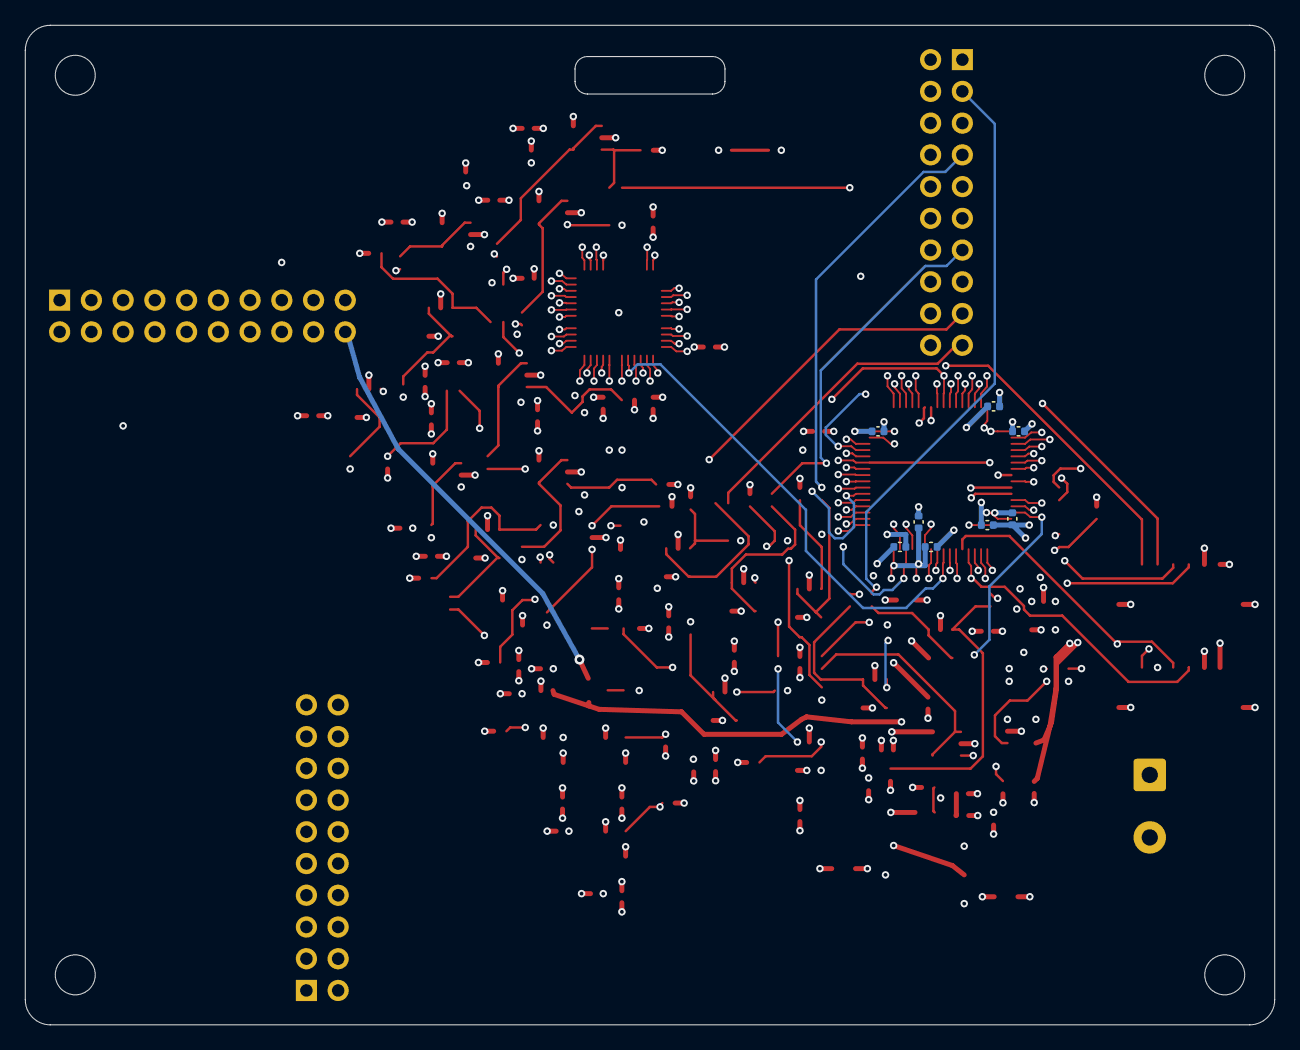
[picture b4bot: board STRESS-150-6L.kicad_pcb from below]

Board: 6 copper layers, 100.0 x 80.0 mm, 154 parts (8 on the bottom side), 132 nets.

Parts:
C1: 10u; C_0805_2012Metric
C2: 22u; C_0805_2012Metric
C3, C10, C11, C12, C13, C14, C15, C16, C17, C30, C31, C32, C33, C34, C40, C50, C51, C52, C53, C100, C101, C102, C103, C104, C105, C106, C107, C108, C109, C110, C111, C112, C113, C114, C115, C116, C117, C118, C119: 100n; C_0402_1005Metric
C18: 4u7; C_0603_1608Metric
C19: 1u; C_0402_1005Metric
D1: green; LED_0603_1608Metric
H1, H2, H3, H4: M-hole 3.2mm; MountingHole_3.2mm_NPTH
J1: 5V IN; TerminalBlock_Phoenix_MKDS-1,5-2_1x02_P5.00mm_Horizontal
J2: OUT1; PinHeader_2x10_P2.54mm_Vertical
J3: OUT2; PinHeader_2x10_P2.54mm_Vertical
J4: AUX; PinHeader_2x10_P2.54mm_Vertical
J5, J6: GH6; JST_GH_SM06B-GHS-TB_1x06-1MP_P1.25mm_Horizontal
R1, R100, R101, R102, R103, R104, R105, R106, R107, R108, R109, R110, R111, R112, R113, R114, R115, R116, R117, R118, R119: 1k; R_0402_1005Metric
R2: 0R; R_0402_1005Metric
R50, R51, R52, R53, R70, R71: 10k; R_0402_1005Metric
R60, R61, R62, R63: 4k7; R_0402_1005Metric
R200, R201, R202, R203, R204, R205, R206, R207, R208, R209, R210, R211, R212, R213, R214, R215, R216, R217, R218, R219: 100R; R_0402_1005Metric
R300, R301, R302, R303, R304, R305, R306, R307, R308, R309, R310, R311, R312, R313, R314, R315, R316, R317, R318, R319: 100k; R_0402_1005Metric
U1: STM32G474RET6; LQFP-64_10x10mm_P0.5mm
U2: STM32F103CBU6; QFN-48-1EP_7x7mm_P0.5mm_EP5.6x5.6mm
U3: AMS1117-3.3; SOT-223-3_TabPin2
U4: LM358; SOIC-8_3.9x4.9mm_P1.27mm
U50, U51, U52, U53: HALL4; HALL4_SMD
U100, U101, U102, U103, U104, U105, U106, U107, U108, U109, U110, U111, U112, U113, U114, U115, U116, U117, U118, U119: MCP6001; SOT-23-5

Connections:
+3V3: C2.1, C10.1, C11.1, C12.1, C13.1, C14.1, C15.1, C16.1, C17.1, C18.1, C19.1, C30.1, C31.1, C32.1, C33.1, C34.1, C50.1, C51.1, C52.1, C53.1, C100.1, C101.1, C102.1, C103.1, C104.1, C105.1, C106.1, C107.1, C108.1, C109.1, C110.1, C111.1, C112.1, C113.1, C114.1, C115.1, C116.1, C117.1, C118.1, C119.1, D1.2, J4.19, J5.1, J6.1, R50.1, R51.1, R52.1, R53.1, R60.1, R61.1, R62.1, R63.1, U1.1, U1.16, U1.28, U1.29, U1.32, U1.48, U1.64, U2.1, U2.9, U2.24, U2.36, U2.48, U3.2, U50.1, U51.1, U52.1, U53.1, U100.5, U101.5, U102.5, U103.5, U104.5, U105.5, U106.5, U107.5, U108.5, U109.5, U110.5, U111.5, U112.5, U113.5, U114.5, U115.5, U116.5, U117.5, U118.5, U119.5
+5V: C1.1, C40.1, J1.1, J4.20, R2.1, U3.3, U4.8
AUX00: J4.1, U2.22
AUX01: J4.2, U2.25
AUX02: J4.3, U2.26
AUX03: J4.4, U2.27
AUX04: J4.5, U2.28
AUX05: J4.6, U2.10
AUX06: J4.7, U2.11
AUX07: J4.8, U2.12
AUX08: J4.9, U2.13
AUX09: J4.10, U2.14
AUX10: J4.11, U2.15
AUX11: J4.12, U2.16
BIN00: R100.2, R300.1, U100.3
BIN01: R101.2, R301.1, U101.3
BIN02: R102.2, R302.1, U102.3
BIN03: R103.2, R303.1, U103.3
BIN04: R104.2, R304.1, U104.3
BIN05: R105.2, R305.1, U105.3
BIN06: R106.2, R306.1, U106.3
BIN07: R107.2, R307.1, U107.3
BIN08: R108.2, R308.1, U108.3
BIN09: R109.2, R309.1, U109.3
BIN10: R110.2, R310.1, U110.3
BIN11: R111.2, R311.1, U111.3
BIN12: R112.2, R312.1, U112.3
BIN13: R113.2, R313.1, U113.3
BIN14: R114.2, R314.1, U114.3
BIN15: R115.2, R315.1, U115.3
BIN16: R116.2, R316.1, U116.3
BIN17: R117.2, R317.1, U117.3
BIN18: R118.2, R318.1, U118.3
BIN19: R119.2, R319.1, U119.3
BUF00: R200.1, U100.1, U100.4
BUF01: R201.1, U101.1, U101.4
BUF02: R202.1, U102.1, U102.4
BUF03: R203.1, U103.1, U103.4
BUF04: R204.1, U104.1, U104.4
BUF05: R205.1, U105.1, U105.4
BUF06: R206.1, U106.1, U106.4
BUF07: R207.1, U107.1, U107.4
BUF08: R208.1, U108.1, U108.4
BUF09: R209.1, U109.1, U109.4
BUF10: R210.1, U110.1, U110.4
BUF11: R211.1, U111.1, U111.4
BUF12: R212.1, U112.1, U112.4
BUF13: R213.1, U113.1, U113.4
BUF14: R214.1, U114.1, U114.4
BUF15: R215.1, U115.1, U115.4
BUF16: R216.1, U116.1, U116.4
BUF17: R217.1, U117.1, U117.4
BUF18: R218.1, U118.1, U118.4
BUF19: R219.1, U119.1, U119.4
FB_A: U4.1, U4.2
FB_B: U4.6, U4.7
GND: C1.2, C2.2, C3.2, C10.2, C11.2, C12.2, C13.2, C14.2, C15.2, C16.2, C17.2, C18.2, C19.2, C30.2, C31.2, C32.2, C33.2, C34.2, C40.2, C50.2, C51.2, C52.2, C53.2, C100.2, C101.2, C102.2, C103.2, C104.2, C105.2, C106.2, C107.2, C108.2, C109.2, C110.2, C111.2, C112.2, C113.2, C114.2, C115.2, C116.2, C117.2, C118.2, C119.2, J1.2, J2.2, J2.4, J2.6, J2.8, J2.10, J2.12, J2.14, J2.16, J2.18, J2.20, J3.2, J3.4, J3.6, J3.8, J3.10, J3.12, J3.14, J3.16, J3.18, J3.20, J4.13, J4.14, J4.15, J4.16, J4.17, J4.18, J5.2, J5.MP, J6.2, J6.MP, R1.2, R300.2, R301.2, R302.2, R303.2, R304.2, R305.2, R306.2, R307.2, R308.2, R309.2, R310.2, R311.2, R312.2, R313.2, R314.2, R315.2, R316.2, R317.2, R318.2, R319.2, U1.15, U1.27, U1.31, U1.47, U1.63, U2.8, U2.23, U2.35, U2.47, U2.49, U3.1, U4.4, U50.3, U51.3, U52.3, U53.3, U100.2, U101.2, U102.2, U103.2, U104.2, U105.2, U106.2, U107.2, U108.2, U109.2, U110.2, U111.2, U112.2, U113.2, U114.2, U115.2, U116.2, U117.2, U118.2, U119.2
IO00: R100.1, U1.7
IO01: R101.1, U1.5
IO02: R102.1, U1.6
IO03: R103.1, U1.55
IO04: R104.1, U1.8
IO05: R105.1, U1.9
IO06: R106.1, U1.10
IO07: R107.1, U1.11
IO08: R108.1, U1.22
IO09: R109.1, U1.23
IO10: R110.1, U1.38
IO11: R111.1, U1.39
IO12: R112.1, U1.40
IO13: R113.1, U1.41
IO14: R114.1, U1.52
IO15: R115.1, U1.53
IO16: R116.1, U1.54
IO17: R117.1, U1.2
IO18: R118.1, U1.3
IO19: R119.1, U1.4
IO20: U1.12, U4.3
IO21: U1.13, U4.5
IO22: R50.2, U1.14, U50.2
IO23: R51.2, U1.17, U51.2
IO24: R52.2, U1.18, U52.2
IO25: R53.2, U1.19, U53.2
IO26: J5.3, R60.2, U1.20
IO27: J5.4, R61.2, U1.21
IO28: J6.3, R62.2, U1.42
IO29: J6.4, R63.2, U1.43
IO30: J5.5, U1.44
IO31: J6.5, U1.45
IO32: J5.6, U1.46
IO33: J6.6, U1.49
IO34: R70.1, U1.50
IO35: R71.2, U1.51
IO36: U1.24, U2.5
IO37: U1.25, U2.6
IO38: U1.26, U2.2
IO39: U1.56, U2.3
IO40: U1.57, U2.4
IO41: U1.58, U2.18
IO42: U1.59, U2.19
IO43: U1.60, U2.20
IO44: U1.61, U2.39
IO45: U1.62, U2.40
IO46: U1.30, U2.41
IO47: U1.33, U2.42
IO48: U1.34, U2.43
IO49: U1.35, U2.45
IO50: U1.36, U2.46
IO51: U1.37, U2.21
LED_K: D1.1, R1.1
OUT00: J2.1, R200.2
OUT01: J2.3, R201.2
OUT02: J2.5, R202.2
OUT03: J2.7, R203.2
OUT04: J2.9, R204.2
OUT05: J2.11, R205.2
OUT06: J2.13, R206.2
OUT07: J2.15, R207.2
OUT08: J2.17, R208.2
OUT09: J2.19, R209.2
OUT10: J3.1, R210.2
OUT11: J3.3, R211.2
OUT12: J3.5, R212.2
OUT13: J3.7, R213.2
OUT14: J3.9, R214.2
OUT15: J3.11, R215.2
OUT16: J3.13, R216.2
OUT17: J3.15, R217.2
OUT18: J3.17, R218.2
OUT19: J3.19, R219.2
PRE_A: R70.2, R71.1
VIN: C3.1, R2.2
